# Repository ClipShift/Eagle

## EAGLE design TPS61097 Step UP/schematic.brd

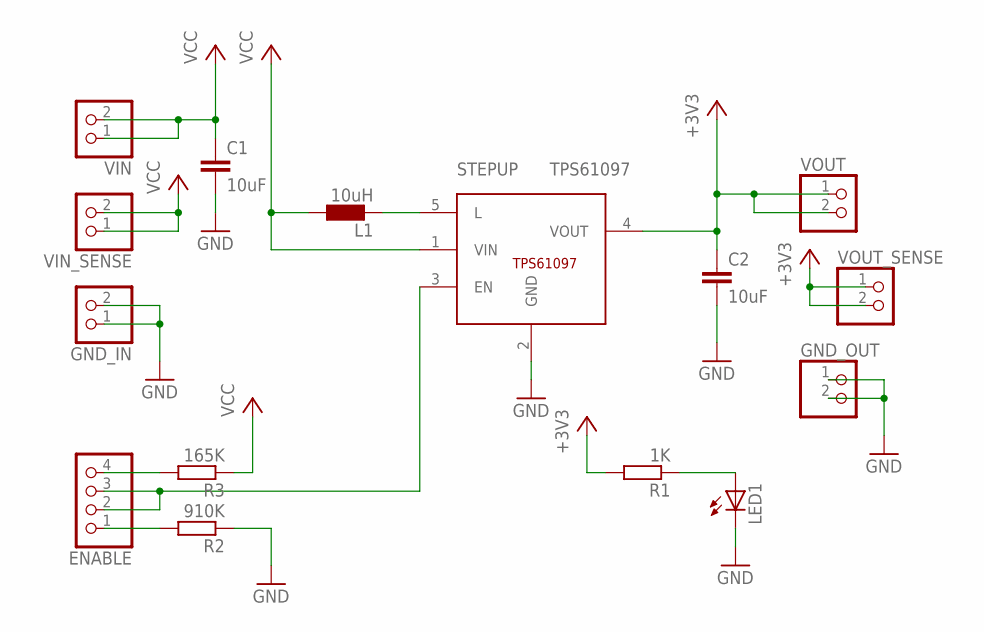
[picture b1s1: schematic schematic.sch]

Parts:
C1, C2: 10uF; C1206
ENABLE: PINHD-1X4; 1X04
GND_IN: PINHD-1X2; 1X02
GND_OUT: PINHD-1X2; 1X02
L1: 10uH; L4532P
LED1: LEDCHIP-LED0805; CHIP-LED0805
R1: 1K; R0805
R2: 910K; R0805
R3: 165K; R0805
STEPUP: TPS61097; SOT-23
VIN: PINHD-1X2; 1X02
VIN_SENSE: PINHD-1X2; 1X02
VOUT: PINHD-1X2; 1X02
VOUT_SENSE: PINHD-1X2; 1X02

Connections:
+3V3: C2.1, R1.2, STEPUP.4 (VOUT), VOUT.1, VOUT.2, VOUT_SENSE.1, VOUT_SENSE.2
GND: C1.2, C2.2, GND_IN.1, GND_IN.2, GND_OUT.1, GND_OUT.2, LED1.C, R2.1, STEPUP.2 (GND)
unnamed: LED1.A, R1.1
unnamed: L1.2, STEPUP.5 (L)
unnamed: ENABLE.2, ENABLE.3, STEPUP.3 (EN)
unnamed: ENABLE.1, R2.2
unnamed: ENABLE.4, R3.2
VCC: C1.1, L1.1, R3.1, STEPUP.1 (VIN), VIN.1, VIN.2, VIN_SENSE.1, VIN_SENSE.2

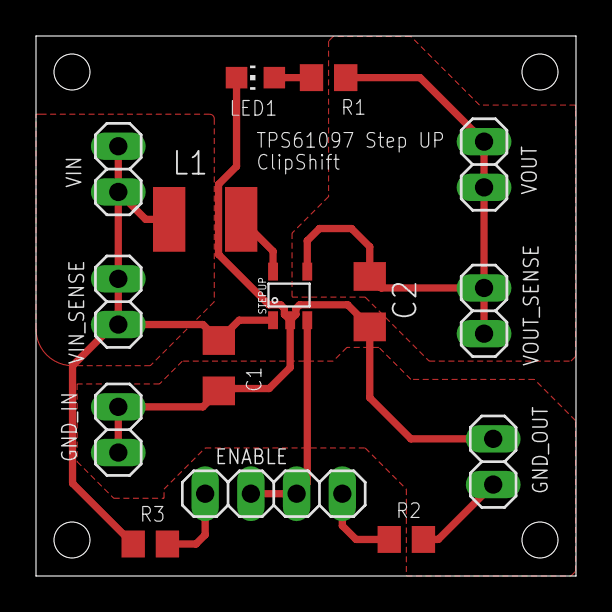
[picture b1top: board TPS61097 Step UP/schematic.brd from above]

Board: 2 copper layers, 30.0 x 30.0 mm, 15 parts (0 on the bottom side), 8 nets.

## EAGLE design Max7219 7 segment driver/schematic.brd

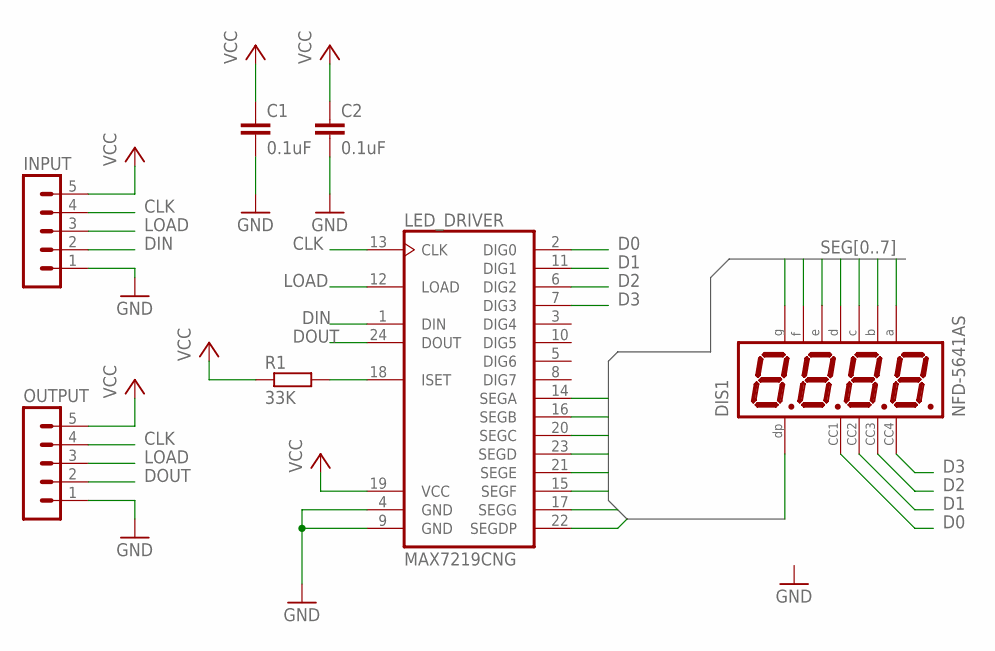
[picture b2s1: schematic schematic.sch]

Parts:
C1, C2: 0.1uF; C025-025X050
DIS1: NFD-5641AS; NFD-5641
INPUT: MA05-1
LED_DRIVER: MAX7219CNG; DIL24-3
OUTPUT: MA05-1
R1: 33K; 0207/10

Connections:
CLK: INPUT.4, LED_DRIVER.13 (CLK), OUTPUT.4
D0: DIS1.P$12, LED_DRIVER.2 (DIG0)
D1: DIS1.P$9, LED_DRIVER.11 (DIG1)
D2: DIS1.P$8, LED_DRIVER.6 (DIG2)
D3: DIS1.P$6, LED_DRIVER.7 (DIG3)
DIN: INPUT.2, LED_DRIVER.1 (DIN)
DOUT: LED_DRIVER.24 (DOUT), OUTPUT.2
GND: C1.2, C2.2, INPUT.1, LED_DRIVER.4 (GND), LED_DRIVER.9 (GND), OUTPUT.1
LOAD: INPUT.3, LED_DRIVER.12 (LOAD), OUTPUT.3
unnamed: LED_DRIVER.18 (ISET), R1.2
SEG0: DIS1.P$11, LED_DRIVER.14 (SEGA)
SEG1: DIS1.P$7, LED_DRIVER.16 (SEGB)
SEG2: DIS1.P$4, LED_DRIVER.20 (SEGC)
SEG3: DIS1.P$2, LED_DRIVER.23 (SEGD)
SEG4: DIS1.P$1, LED_DRIVER.21 (SEGE)
SEG5: DIS1.P$10, LED_DRIVER.15 (SEGF)
SEG6: DIS1.P$5, LED_DRIVER.17 (SEGG)
SEG7: DIS1.P$3, LED_DRIVER.22 (SEGDP)
VCC: C1.1, C2.1, INPUT.5, LED_DRIVER.19 (VCC), OUTPUT.5, R1.1

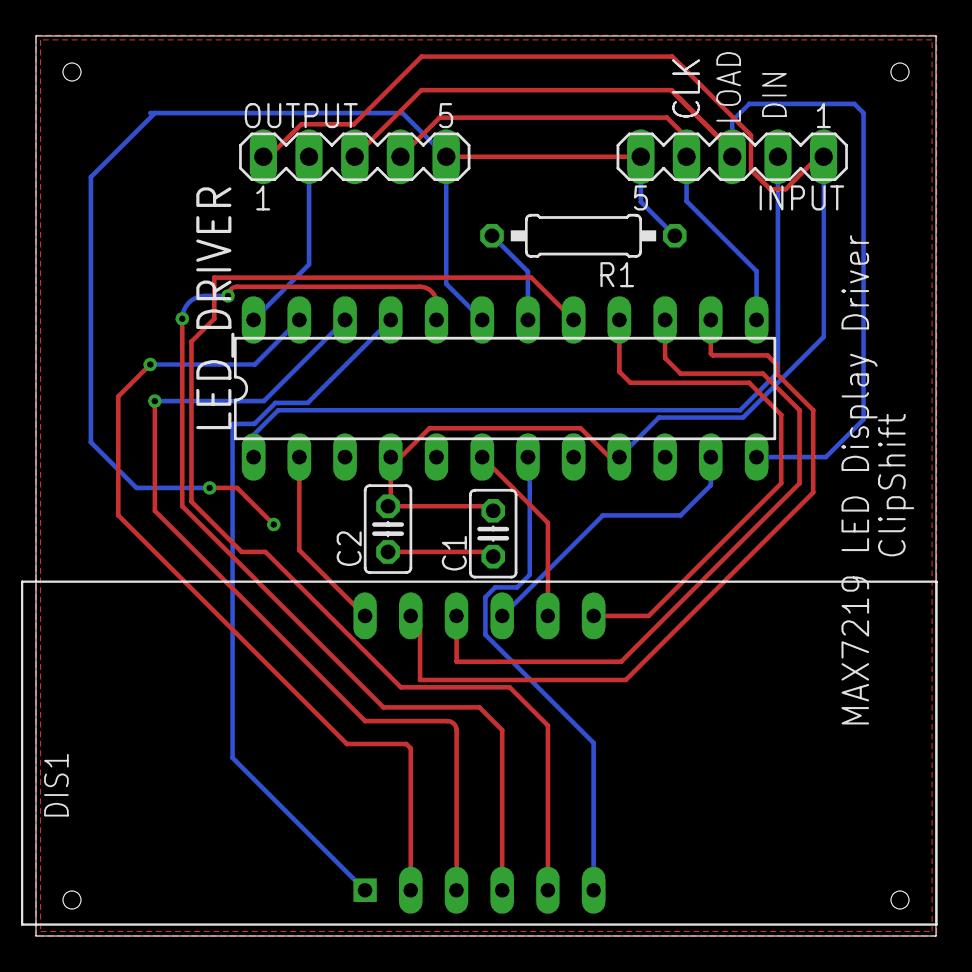
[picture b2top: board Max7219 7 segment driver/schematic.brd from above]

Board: 2 copper layers, 50.0 x 50.0 mm, 7 parts (0 on the bottom side), 19 nets.
